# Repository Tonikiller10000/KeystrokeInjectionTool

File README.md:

# KeystrokeInjectionTool

## KeystrokeInjectionTool_V1.0
The first board was made at home in an arduino shield form put over an arduino uno. 
The projection was printed on the [heat tstransfer paper](https://github.com/Tonikiller10000/KeystrokeInjectionTool/blob/main/KeystrokeInjectionTool_V1.0/KeystrokeInjectionTool_Pictures/f.jpg) at the printer, after witch I put the [print on](https://github.com/Tonikiller10000/KeystrokeInjectionTool/blob/main/KeystrokeInjectionTool_V1.0/KeystrokeInjectionTool_Pictures/ff.jpg), by pressing the copper on a smd soldering plate. 
After the print is on the copper, the board was put in the feric clorhide and then cleaned. Then I drilled the holes of the [board](https://github.com/Tonikiller10000/KeystrokeInjectionTool/blob/main/KeystrokeInjectionTool_V1.0/KeystrokeInjectionTool_Pictures/fff.jpg), and [soldered](https://github.com/Tonikiller10000/KeystrokeInjectionTool/blob/main/KeystrokeInjectionTool_V1.0/KeystrokeInjectionTool_Pictures/c4.jpg) the smd and tht parts in this order. 
After [cleaning](https://github.com/Tonikiller10000/KeystrokeInjectionTool/blob/main/KeystrokeInjectionTool_V1.0/KeystrokeInjectionTool_Pictures/ffff.jpg), the board was [ready](https://github.com/Tonikiller10000/KeystrokeInjectionTool/blob/main/KeystrokeInjectionTool_V1.0/KeystrokeInjectionTool_Pictures/c22.jpg) for soldering. 

## The KeystrokeInjectionTool_V1.0 in action
This board was made from an arduino uno with this [homemade shield](https://github.com/Tonikiller10000/KeystrokeInjectionTool/blob/main/KeystrokeInjectionTool_V1.0/KeystrokeInjectionTool_Pictures/fffff.jpg) with buttons to activate the keystrokes comands.
The board worked pretty well, but sometimes, the keystrokes beginned faster and the program didn\`t run well. 
Here are 2 videos with the board being tested at home as a keyboard with keys and shortcuts 
[Vid1](https://github.com/Tonikiller10000/KeystrokeInjectionTool/blob/main/KeystrokeInjectionTool_V1.0/KeystrokeInjectionTool_Pictures/f1.mp4), 
[Vid2](https://github.com/Tonikiller10000/KeystrokeInjectionTool/blob/main/KeystrokeInjectionTool_V1.0/KeystrokeInjectionTool_Pictures/f2.mp4).

<table>
  <tr>
    <td></td>
    <td></td>
  </tr>
 </table>

## KeystrokeInjectionTool_V2.0
This board was designed like a normal USB Memory Stick. It has 2 dip switches and a [push button](https://github.com/Tonikiller10000/KeystrokeInjectionTool/blob/main/KeystrokeInjectionTool_V2.0/KeystrokeInjTool_Pictures/KS1.jpg) 
for user input, the ATTINY85 or ATTINY45 microcontroller, and an 256Kb I2C EEPROM for additional 256Kb of memmory. 
The stick case will have a sliding mechanism to have a steady grip instead of using holes. 
Now I have to wait the board to arrive and start working on it\`s case.

<table>
  <tr>
    <td></td>
    <td></td>
    <td></td>
  </tr>
</table>

## Schematic:

## Mentions:
- If I was to use an SD card instead of an I2C EEPROM, I wold\`ve needed 4 pins witch means I couldn\`t use the 4 switchees for code execution select. 
Maybe If someone want\`s to try with an aditional small IC to convert the SPI from the SD card to the I2C for the microcontroller. 
It would be in size like the current EEPROM and on the back of the device would be the SD socket.

- an upgrade would be using an stm32 as a keystroke injection tool.
The stm32 is capable of USB, SD card, buttons and leds at the same time and can do more advanced stuff hardware and software 
(you can also add a small i2c oled screen 32x128 to display witch code to execute. 
but that would require a small battery like a earbuud one or a coin one, or editing options after connection. 
with stm32 the keystoke injection tool can apear as a drive too and you can do something to copy the data on it.)

## Links:
- recomended video: https://youtu.be/XwEZvaGyKDE?si=0O5bhv-sC-1KsNow
- the basic schematic diagram: https://github.com/Tonikiller10000/KeystrokeInjectionTool/blob/main/KeystrokeInjectionTool_V2.0/KeystrokeInjTool_Pictures/p1.jpg
- CAT24C256(256Kb I2C EEPROM) datasheet: https://www.onsemi.com/pdf/datasheet/cat24c256-d.pdf

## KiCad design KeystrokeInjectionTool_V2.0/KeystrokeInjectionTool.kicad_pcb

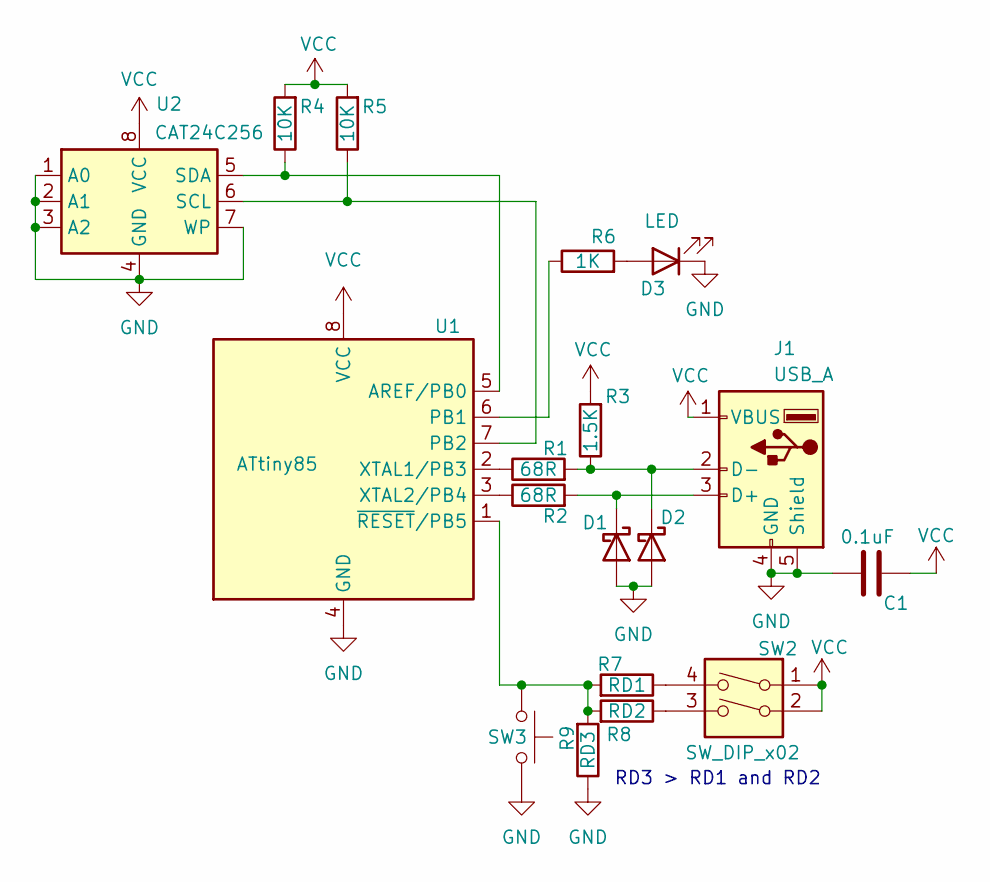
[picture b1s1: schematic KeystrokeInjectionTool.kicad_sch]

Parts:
C1: 0.1uF; C_0805_2012Metric_Pad1.18x1.45mm_HandSolder
D1, D2: 1N5711UR; D_0603_1608Metric_Pad1.05x0.95mm_HandSolder
D3: LED
J1: USB_A; USB_A_CNCTech_1001-011-01101_Horizontal
R1, R2: 68R; R_0603_1608Metric_Pad0.98x0.95mm_HandSolder
R3: 1.5K; R_0603_1608Metric_Pad0.98x0.95mm_HandSolder
R4, R5: 10K; R_0603_1608Metric_Pad0.98x0.95mm_HandSolder
R6: 1K; R_0603_1608Metric_Pad0.98x0.95mm_HandSolder
R7: RD1; R_0603_1608Metric_Pad0.98x0.95mm_HandSolder
R8: RD2; R_0603_1608Metric_Pad0.98x0.95mm_HandSolder
R9: RD3; R_0603_1608Metric_Pad0.98x0.95mm_HandSolder
SW2: SW_DIP_x02
SW3: SW_Push
U1: ATtiny85; SOIC-8W_5.3x5.3mm_P1.27mm
U2: CAT24C256; SOIC-8_3.9x4.9mm_P1.27mm

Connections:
GND: C1.1, D1.2 (A), D2.2 (A), D3.1 (K), J1.4 (GND), J1.5 (Shield), R9.1, SW3.1, U1.4 (GND), U2.1 (A0), U2.2 (A1), U2.3 (A2), U2.4 (GND), U2.7 (WP); also elsewhere on the board
unnamed: D1.1 (K), J1.3 (D+), R2.2
unnamed: D2.1 (K), J1.2 (D-), R1.2, R3.1
unnamed: D3.2 (A), R6.2
unnamed: R7.1, SW2.4
unnamed: R8.1, SW2.3
unnamed: R4.1, U1.5 (AREF/PB0), U2.5 (SDA)
unnamed: R6.1, U1.6 (PB1)
unnamed: R5.1, U1.7 (PB2), U2.6 (SCL)
unnamed: R1.1, U1.2 (XTAL1/PB3)
unnamed: R2.1, U1.3 (XTAL2/PB4)
unnamed 11: R7.2, R8.2, R9.2, SW3.2, U1.1 (~RESET/PB5); also elsewhere on the board
VCC: C1.2, J1.1 (VBUS), R3.2, R4.2, R5.2, SW2.1, SW2.2, U1.8 (VCC), U2.8 (VCC)

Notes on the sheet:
RD3 > RD1 and RD2

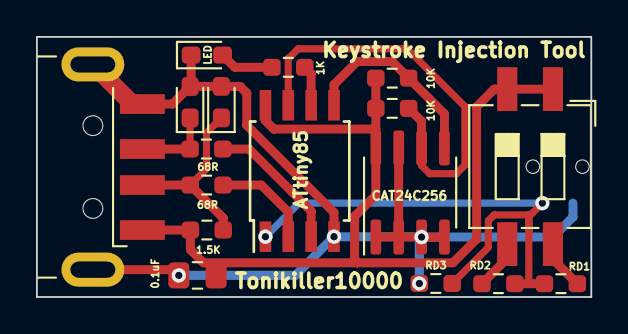
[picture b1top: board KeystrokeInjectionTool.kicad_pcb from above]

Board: 2 copper layers, 30.8 x 14.5 mm, 18 parts (1 on the bottom side), 13 nets.

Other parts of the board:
SW1: SW_Push; Panasonic_EVQPUL_EVQPUC

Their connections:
GND: SW1.1; also elsewhere on the board
unnamed 11: SW1.2; also elsewhere on the board

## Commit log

2026-06-30 dfsf
2026-06-30 d
    d
